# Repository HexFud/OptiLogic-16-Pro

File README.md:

# OptiLogic-16 Pro

OptiLogic-16 Pro is a custom built, FPGA-based 16-channel logic analyzer and network monitor designed from scratch from PCB design and component selection to firmware development and 3D modeling.
Featuring a Xilinx Kintex-7 FPGA 500 MSa/s sampling programmable input thresholds 4 Gbit DDR3 memory three SFP ports Gigabit Ethernet and USB 3.0, it is designed for high-speed digital signal analysis, hardware debugging, and network data acquisition.

## Schematic and PCB

### How this was made

I designed an 8-layer PCB that has 16 digital inputs united by 4 comparators. The board runs with 12V DC current with a standard barrel jack connector:

1. 16 analog thresholds programmable from -2.0V to +5.0V.
2. A 4 Gbit DDR3 memory dedicated to sample buffering.
3. Three SFP cages for fiber optic (2 are recive only and 1 is recive and trasmit).
4. Gigabit Ethernet.
5. USB 3.0 for PC communication.

The PCB has a precise layer structure:

1. **F.Cu** is only used for local connections or high speed and GND plane
2. **In1.Cu** is used as GND plane to remove noise and interferences from the under and above layer. It is used to put traces on it if there is no space between them
3. **In2.Cu** is used for short range high speed comunication like the RAM
4. **In3.Cu** is used only to carry power with very thick copper traces
5. **In4.Cu** is the same as In1.Cu
6. **In5.Cu** used to connect the comparators and DACs between them and wire them to the FGPA
7. **In6.Cu** is the same as In3.Cu
8. **B.Cu** used as auxiliary short distance traces

### External connections breakdown

1. **12V Power**: The main barrel jack socket that powers the board portectd by a resettable fuse. The 12V input is stepped down with multiple converters and the 12V input becomes +7.0V, -3.0V, +3.3V, +2.5V, +1.8V, +1.5V, +1.2V, +1.0V required by the FPGA, comparators, and transceivers.
2. **USB-C Port**: This port supports PC communication.
3. **Logic Probes**: Two 20-pin headers handling the 16 high-speed input channels. The even pins are connected to GND.
4. **JTAG**: A 14-pin socket used to debug and flash the FPGA and the QSPI memory.

### Mechanical design and why I chose certain components

To make sure the logic analyzer can sample at 500 MSa/s without struggling with signal integrity, I had to select specialized components:

* **FPGA (Xilinx Kintex-7 XC7K70T-2FBG676I)**: I choose the FBG676 package because it provides enough I/O pins to drive everything that is on the board.
* **Comparators (LMH7324)**: Selected for their 700 ps rise/fall times. By powering their output stage (`VCCO`) at +2.5V, the RSPECL outputs naturally shift to LVDS levels, allowing direct connection to the FPGA without complex external resistor networks.
* **USB Bridge (FTDI FT601Q)**: I avoided using a PCIe interface or a complex FPGA-based USB PHY. The FT601Q provides a 32-bit synchronous 245 FIFO interface running at 100 MHz, easily sustaining ~380 MB/s of real-world bandwidth to the host PC.
* **DACs (TI DAC8568)**: Chosen to provide 16 independent threshold voltages. A single SPI bus configures both chips, and precision Op-Amps scale the 0–2.5V output to the required -2.0V to +5.0V range.

### How to flash the firmware

My project doesn't have a built-in USB-to-JTAG programmer. To flash the firmware you need a Xilinx Platform Cable USB or a JTAG adapter wired to the connector. You must use the AMD/Xilinx Vivado Design Suite to upload the firmware into the QSPI Flash.

### Steps to reproduce:

**In AMD/Xilinx Vivado (Compilation):**

1. Install Vivado 2023.2 (or newer).
2. Open the project and go to the settings to select the target device `XC7K70T-2FBG676I`.
3. Add the Verilog sources and the XDC file.
4. Run Synthesis and Implementation from the left panel.
5. Click on Generate Bitstream.
6. Open the Tcl Console and paste the following command to export the compiled binary for the QSPI Flash:
`write_cfgmem -format bin -interface spix4 -size 16 -loadbit "up 0x0 ./project_name.runs/impl_1/optilogic_16_pro_top.bit" -file ./optilogic_16_pro_flash.bin`

**In Vivado Hardware Manager (Flashing):**

1. Insert the JTAG programmer into the PC and connect it to the header on the board.
2. Connect the 12V power supply.
3. In Vivado, click "Open Hardware Manager" ensure that the programmer is selected, and click "Auto Connect".
4. Right-click the `xc7k70t_0` device and select "Add Configuration Memory Device".
5. Search for the `w25q128-spi-x1_x2_x4` part and select it.
6. Go to the programming tab select the previously exported `.bin` file ensure "Erase, Program, Verify" is selected, and click "Start Programming". If everything goes right you'll see a success message. Power-cycle the board to boot the firmware.

### Filament and Thermal recommendation

The Kintex-7 FPGA, FT601Q bridge, KSZ9031 PHY, and switching regulators generate a lot of heat (50°C–60°C) during continuous sampling. The LMH7324 comparators also dissipate heat into the PCB internal GND plane. To dissipate the thermal load and shield the board from radio frequency interference the board must be enclosed in a CNC-machined aluminum case.
I suggest using these settings on JLCPCB before putting it into production

### ⚠️⚠️ Safety advice ⚠️⚠️

This project includes experimental software and hardware designs. Assembly documentation and firmware are still under development and may contain bugs, errors, or incomplete features. By using, building, or modifying this project, you acknowledge that:

1. You use this project entirely at your own risk.
2. You are solely responsible for safe assembly, testing, and operation.
3. The author isn't responsible for any type of damage, injury, or loss to people or the machine itself.

By proceeding, you accept all risks and agree to these conditions. If you do not acknowledge these risks and conditions, please do not use or build this project.

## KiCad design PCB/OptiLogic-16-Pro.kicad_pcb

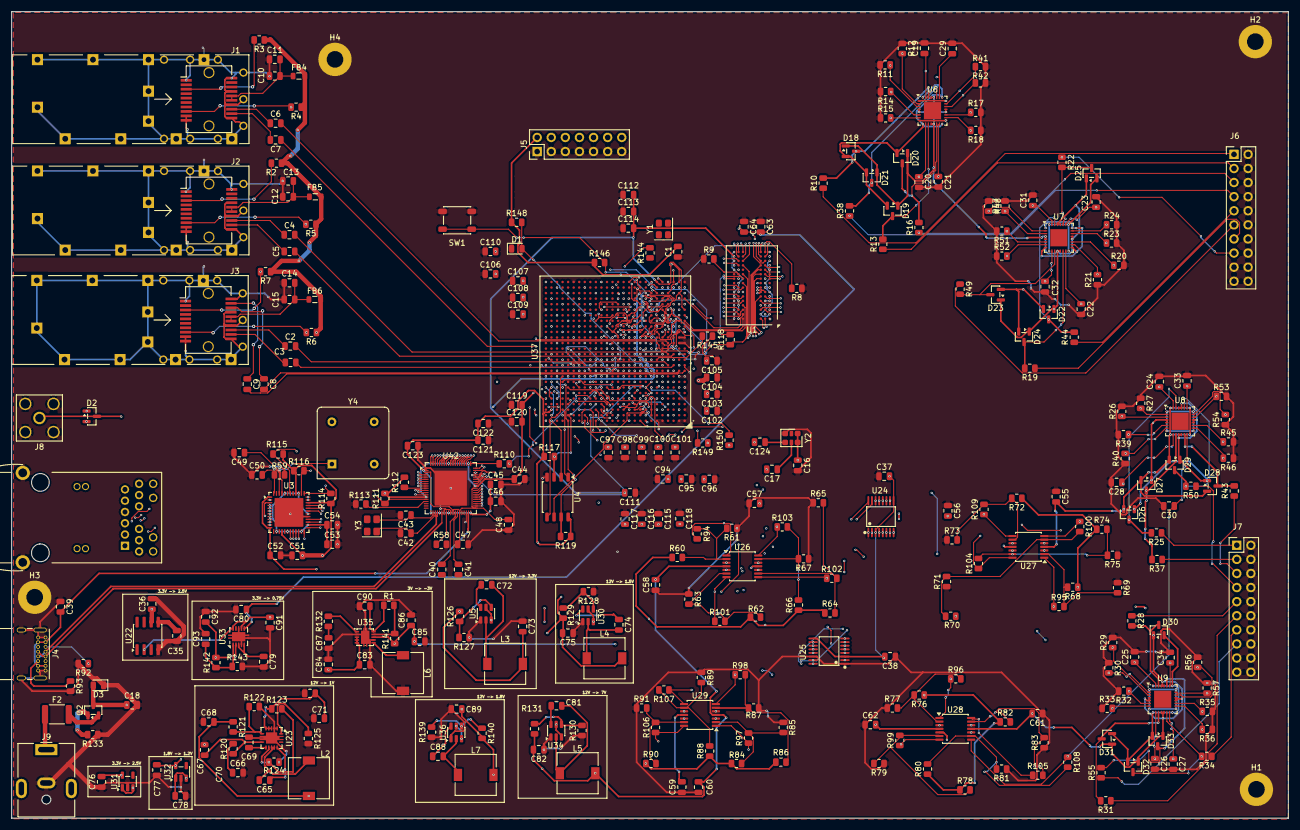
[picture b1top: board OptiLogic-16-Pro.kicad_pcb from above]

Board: 8 copper layers, 230.0 x 145.3 mm, 342 parts (0 on the bottom side), 339 nets.

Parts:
C1, C2, C3, C4, C5, C6, C7, C8, C9, C10, C12, C14, C16, C17, C19, C20, C21, C22, C23, C24, C25, C26, C27, C28, C29, C30, C31, C32, C33, C34, C37, C38, C39, C40, C41, C44, C45, C46, C48, C51, C52, C53, C55, C56, C57, C58, C59, C60, C61, C62, C63, C64, C65, C72, C74, C80, C81, C84, C88, C90, C91, C93, C94, C95, C96, C97, C98, C99, C100, C101, C102, C103, C106, C107, C108, C109, C111, C112, C113, C114, C115, C116, C117, C118, C119, C120, C121, C122, C123, C124: 100nF; C_0805_2012Metric
C11, C13, C15, C79, C83, C85, C86: 10uF; C_0805_2012Metric
C18: 100uF 25V; C_0805_2012Metric
C35, C36, C78, C92: 1uF; C_0805_2012Metric
C42, C43: 12pF; C_0805_2012Metric
C47, C54, C70, C71, C104, C105, C110: 4.7uF; C_0805_2012Metric
C49, C50: 22pF; C_0805_2012Metric
C66: 27nF; C_0805_2012Metric
C67: 43pF; C_0805_2012Metric
C68: 100uF; C_0805_2012Metric
C69: 2.2nF; C_0805_2012Metric
C73, C75, C82, C89: 22uF; C_0805_2012Metric
C76, C77: 2.2uF; C_0805_2012Metric
C87: 1nF; C_0805_2012Metric
D1: LED; LED_0805_2012Metric
D2, D18, D19, D20, D21, D22, D23, D24, D25, D26, D27, D28, D29, D30, D31, D32, D33: BAV99; SOT-23
D3: 18V; D_0805_2012Metric
F2: 3A 16V; Fuse_1812_4532Metric
FB4, FB5, FB6: FerriteBead; L_0805_2012Metric
H1, H2, H3, H4: MountingHole_Pad; MountingHole_3mm_Pad
J1, J2, J3: SFP; Connector_SFP_and_Cage
J4: USB_C_Receptacle; USB_C_Receptacle_GCT_USB4085
J5: Conn_02x07_Odd_Even; PinHeader_2x07_P2.54mm_Vertical
J6, J7: Conn_02x10_Odd_Even; PinHeader_2x10_P2.54mm_Vertical
J8: Conn_Coaxial; SMA_Amphenol_132203-12_Horizontal
J9: Barrel_Jack; BarrelJack_CUI_PJ-063AH_Horizontal
L2, L3, L5: 2.2uH; L_7.3x7.3_H3.5
L4, L7: 1.5uH; L_7.3x7.3_H3.5
L6: 4.7uH; L_7.3x7.3_H3.5
Q2: Q_PMOS_GSD; SOT-23
R1: 12.1k; R_0805_2012Metric
R2, R3, R4, R5, R6, R7, R8, R114: 4.7K; R_0805_2012Metric
R9: 240; R_0805_2012Metric
R10, R13, R16, R19, R22, R25, R28, R31, R34, R37, R38, R43, R44, R49, R50, R55, R118, R145: 100; R_0805_2012Metric
R11, R12, R14, R15, R17, R18, R20, R21, R23, R24, R26, R27, R29, R30, R32, R33, R35, R36, R39, R40, R41, R42, R45, R46, R47, R48, R51, R52, R53, R54, R56, R57: 150; R_0805_2012Metric
R58: 12k 1%; R_0805_2012Metric
R59: 12.1k 1%; R_0805_2012Metric
R60, R62, R64, R66, R68, R70, R72, R74, R76, R78, R80, R82, R84, R86, R88, R90: 15k 0.1%; R_0805_2012Metric
R61, R63, R65, R67, R69, R71, R73, R75, R77, R79, R81, R83, R85, R87, R89, R91, R94, R95, R96, R97, R98, R99, R100, R101, R102, R103, R104, R105, R106, R107, R108, R109: 12k 0.1%; R_0805_2012Metric
R92, R93: 5.1k; R_0805_2012Metric
R110: 22; R_0805_2012Metric
R111, R112, R113, R127, R128, R129, R130, R139, R142, R143: 10k; R_0805_2012Metric
R115, R116, R122: 10K; R_0805_2012Metric
R117, R119, R132, R146, R148, R149, R150: 4.7k; R_0805_2012Metric
R120: 3.57k; R_0805_2012Metric
R121: 2.49K; R_0805_2012Metric
R123: 102k; R_0805_2012Metric
R124: 36.5k; R_0805_2012Metric
R125: 107k; R_0805_2012Metric
R126: 33.2k; R_0805_2012Metric
R131: 82.5k; R_0805_2012Metric
R133: 100k; R_0805_2012Metric
R140: 13.7k; R_0805_2012Metric
R141: 30k; R_0805_2012Metric
R144: 33; R_0805_2012Metric
RJ1: RJ45-TH_0826-1X1T-HT-F
SW1: SW_Push; SW_SPST_PTS647_Sx38
U1: MT41K256M16HA; Micron_FBGA-96_9x14mm_Layout9x16_P0.8mm
U3: KSZ9031RNXCA; QFN-48-1EP_7x7mm_P0.5mm_EP5.15x5.15mm
U4: W25Q128JVS; SOIC-8_5.3x5.3mm_P1.27mm
U5, U30, U34, U36: TPS563200; SOT-23-6
U6, U7, U8, U9: LMH7324; WQFN-32-1EP_5x5mm_P0.5mm_EP3.1x3.1mm
U22: REF5025AD; SOIC-8_3.9x4.9mm_P1.27mm
U23: VQFN-14_L3.5-W3.5-P0.50-BL-EP_TPS54622RHLT
U24, U25: TSSOP-16_L5.0-W4.4-P0.65-LS6.4-BL
U26, U27, U28, U29: Opamp_Quad; TSSOP-14_4.4x5mm_P0.65mm
U31: AP2112K-2.5; SOT-23-5
U32: TLV75512PDBV; SOT-23-5
U33: TPS51200DRC; VSON-10-1EP_3x3mm_P0.5mm_EP1.65x2.4mm
U35: VSON-10_L3.0-W3.0-P0.50-TL-EP-1
U37: FBGA-676_L27.0-W27.0-R26-C26-P1.00-BL
U42: FT601Q; QFN-76-1EP_9x9mm_P0.4mm_EP5.81x6.31mm
Y1: ACO-xxxMHz; Oscillator_SMD_Abracon_ASE-4Pin_3.2x2.5mm
Y2: 125MHz; Oscillator_SMD_SiTime_PQFD-6L_3.2x2.5mm
Y3: Crystal; Crystal_SMD_3225-4Pin_3.2x2.5mm
Y4: 25.000 MHz; Oscillator_DIP-8

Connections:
+0V75_VREF: C63.2, C64.2, C80.1, U1.H1 (V_{REFDQ}), U1.M8 (V_{REFCA}), U33.6 (REFOUT)
+0V75_VTT: C79.1, U33.3 (VO), U33.5 (VOSNS)
+1V0: C68.2, C94.2, C95.2, C96.2, C97.2, C98.2, C99.2, C100.2, C101.2, C102.2, C103.2, C104.2, C105.2, L2.2, R121.1, U37.C6 (MGTAVCC), U37.E6 (MGTAVCC), U37.G6 (MGTAVCC), U37.J6 (MGTAVCC), U37.J9 (VCCINT), U37.K8 (VCCINT), U37.K10 (VCCINT), U37.K12 (VCCINT), U37.K14 (VCCINT), U37.L6 (MGTAVCC), U37.L9 (VCCINT), U37.L13 (VCCINT), U37.L15 (VCCINT), U37.M8 (VCCINT), U37.M14 (VCCINT), U37.N9 (VCCINT), U37.N13 (VCCBRAM), U37.N15 (VCCINT), U37.P14 (VCCINT), U37.R13 (VCCBRAM), U37.R15 (VCCINT), U37.T12 (VCCBRAM), U37.T14 (VCCINT), U37.U13 (VCCBRAM), U37.U15 (VCCINT)
+1V2: C53.1, C54.1, C77.2, C115.2, C116.2, C117.2, C118.2, U3.4 (AVDDL), U3.9 (AVDDL), U3.14 (DVDDL), U3.18 (DVDDL), U3.23 (DVDDL), U3.26 (DVDDL), U3.30 (DVDDL), U3.39 (DVDDL), U3.44 (AVDDL_PLL), U32.5 (OUT), U37.B3 (MGTAVTT), U37.C2 (MGTAVTT), U37.D3 (MGTAVTT), U37.G2 (MGTAVTT), U37.H3 (MGTAVTT), U37.L2 (MGTAVTT), U37.M3 (MGTAVTT), U37.M5 (MGTAVTTRCAL_115)
+1V5: C75.2, C92.2, C111.2, C112.2, C113.2, C114.2, L4.2, R129.2, R142.2, U1.A1 (V_{DDQ}), U1.A8 (V_{DDQ}), U1.B2 (V_{DD}), U1.C1 (V_{DDQ}), U1.C9 (V_{DDQ}), U1.D2 (V_{DDQ}), U1.D9 (V_{DD}), U1.E9 (V_{DDQ}), U1.F1 (V_{DDQ}), U1.G7 (V_{DD}), U1.H2 (V_{DDQ}), U1.H9 (V_{DDQ}), U1.K2 (V_{DD}), U1.K8 (V_{DD}), U1.N1 (V_{DD}), U1.N9 (V_{DD}), U1.R1 (V_{DD}), U1.R9 (V_{DD}), U33.2 (VLDOIN), U37.AA1 (VCCO_34), U37.AC5 (VCCO_34), U37.AD2 (VCCO_34), U37.AF6 (VCCO_34), U37.U3 (VCCO_34), U37.Y4 (VCCO_34)
+1V8: C78.2, C89.2, C106.2, C107.2, C108.2, C109.2, C110.2, L7.2, R140.2, U32.1 (IN), U32.3 (EN), U37.AA11 (VCCO_33), U37.AB8 (VCCO_33), U37.AB18 (VCCO_32), U37.AC15 (VCCO_32), U37.AD12 (VCCO_33), U37.AE9 (VCCO_33), U37.AE19 (VCCO_32), U37.AF16 (VCCO_32), U37.L11 (VCCAUX), U37.M10 (VCCAUX), U37.N6 (MGTVCCAUX), U37.P8 (VCCAUX_IO_G0), U37.P10 (VCCAUX), U37.R9 (VCCAUX_IO_G0), U37.T8 (VCCAUX_IO_G0), U37.T10 (VCCAUX), U37.U11 (VCCAUX), U37.V10 (VCCO_33), U37.W7 (VCCO_33), U37.W17 (VCCO_32), U37.Y14 (VCCO_32)
+2V5: C44.1, C51.2, C76.2, C119.2, C120.2, R111.2, R112.2, R114.1, R115.1, R116.1, U3.16 (DVDDH), U3.34 (DVDDH), U3.40 (DVDDH), U6.1 (VCCO), U6.8 (VCCO), U6.17 (VCCO), U6.24 (VCCO), U7.1 (VCCO), U7.8 (VCCO), U7.17 (VCCO), U7.24 (VCCO), U8.1 (VCCO), U8.8 (VCCO), U8.17 (VCCO), U8.24 (VCCO), U9.1 (VCCO), U9.8 (VCCO), U9.17 (VCCO), U9.24 (VCCO), U31.5 (VOUT), U37.A11 (VCCO_16), U37.AA21 (VCCO_12), U37.AC25 (VCCO_12), U37.AD22 (VCCO_12), U37.AF26 (VCCO_12), U37.B8 (VCCO_16), U37.B18 (VCCO_15), U37.C15 (VCCO_16), U37.D12 (VCCO_16), U37.E9 (VCCO_16), U37.E19 (VCCO_15), U37.F16 (VCCO_15), U37.G13 (VCCO_16), U37.H10 (VCCO_16), U37.H20 (VCCO_15), U37.J17 (VCCO_15), U37.K24 (VCCO_13), U37.M18 (VCCO_15), U37.N25 (VCCO_13), U37.P22 (VCCO_13), U37.R19 (VCCO_13), U37.T16 (VCCO_13), U37.T26 (VCCO_13), U37.U23 (VCCO_12), U37.V20 (VCCO_12), U37.Y24 (VCCO_12), U42.14 (VCCIO), U42.49 (VCCIO), U42.59 (VCCIO), U42.68 (VCCIO)
+3V3: C1.2, C16.1, C37.2, C38.2, C45.1, C46.1, C52.1, C73.2, C83.1, C84.1, C91.1, C121.2, C122.2, C123.2, FB4.2, FB5.2, FB6.2, J5.2, L3.2, R2.1, R3.1, R4.1, R5.1, R6.1, R7.1, R117.1, R119.1, R126.2, R146.1, R148.1, R149.1, R150.1, U3.1 (AVDDH), U3.12 (AVDDH), U4.8 (VCC), U22.2 (Vin), U24.3 (AVDD), U24.9 (CLR#), U25.3 (AVDD), U25.9 (CLR#), U31.1 (VIN), U31.3 (EN), U33.7 (EN), U33.10 (VIN), U35.3 (VIN), U35.4 (EN), U35.5 (IN), U37.A21 (VCCO_14), U37.C25 (VCCO_14), U37.D22 (VCCO_14), U37.E8 (VCCBATT_0), U37.F26 (VCCO_14), U37.G23 (VCCO_14), U37.L7 (VCCO_0), U37.L21 (VCCO_14), U37.P7 (CFGBVS_0), U37.T6 (VCCO_0), U42.2 (AVDD), U42.20 (VCC33), U42.24 (VCC33), U42.28 (VDDA), U42.38 (VCC33), Y2.1 (OE), Y2.6 (VDD)
+7V0_A: C55.2, C58.2, C60.2, C62.2, C82.2, D2.2 (A), D18.2 (A), D19.2 (A), D20.2 (A), D21.2 (A), D22.2 (A), D23.2 (A), D24.2 (A), D25.2 (A), D26.2 (A), D27.2 (A), D28.2 (A), D29.2 (A), D30.2 (A), D31.2 (A), D32.2 (A), D33.2 (A), L5.2, R131.2, U6.9 (VCCI), U6.16 (VCCI), U6.25 (VCCI), U6.32 (VCCI), U7.9 (VCCI), U7.16 (VCCI), U7.25 (VCCI), U7.32 (VCCI), U8.9 (VCCI), U8.16 (VCCI), U8.25 (VCCI), U8.32 (VCCI), U9.9 (VCCI), U9.16 (VCCI), U9.25 (VCCI), U9.32 (VCCI), U26.4 (V+), U27.4 (V+), U28.4 (V+), U29.4 (V+)
+12V_RAW: C18.1, C70.2, C71.2, D3.2 (A2), Q2.3 (D), R123.1, U5.3 (VIN), U5.5 (EN), U23.4 (PVIN), U23.5 (PVIN), U23.6 (VIN), U30.3 (VIN), U30.5 (EN), U34.3 (VIN), U34.5 (EN), U36.3 (VIN), U36.5 (EN)
-3V0_A: C56.2, C57.2, C59.2, C61.2, C85.1, C86.1, D2.1 (K), D18.1 (K), D19.1 (K), D20.1 (K), D21.1 (K), D22.1 (K), D23.1 (K), D24.1 (K), D25.1 (K), D26.1 (K), D27.1 (K), D28.1 (K), D29.1 (K), D30.1 (K), D31.1 (K), D32.1 (K), D33.1 (K), R141.1, U6.4 (VEE), U6.5 (VEE), U6.12 (VEE), U6.13 (VEE), U6.20 (VEE), U6.21 (VEE), U6.28 (VEE), U6.29 (VEE), U7.4 (VEE), U7.5 (VEE), U7.12 (VEE), U7.13 (VEE), U7.20 (VEE), U7.21 (VEE), U7.28 (VEE), U7.29 (VEE), U8.4 (VEE), U8.5 (VEE), U8.12 (VEE), U8.13 (VEE), U8.20 (VEE), U8.21 (VEE), U8.28 (VEE), U8.29 (VEE), U9.4 (VEE), U9.5 (VEE), U9.12 (VEE), U9.13 (VEE), U9.20 (VEE), U9.21 (VEE), U9.28 (VEE), U9.29 (VEE), U26.11 (V-), U27.11 (V-), U28.11 (V-), U29.11 (V-), U35.8 (OUT)
/Power_Supply/EN: R123.2, R124.1, U23.10 (EN)
/Power_Supply/FB: R1.2, R141.2, U35.9 (FB)
/Power_Supply/REFIN: C93.1, R142.1, R143.1, U33.1 (REFIN)
/Power_Supply/VREF: C90.2, R1.1, U35.10 (VREF)
/Power_Supply/VSENSE: R121.2, R122.1, U23.7 (VSENSE)
DAC_CS0_N: U24.2 (SYNC#), U37.G24 (IO_L14P_T2_SRCC_14)
DAC_CS1_N: U25.2 (SYNC#), U37.F24 (IO_L14N_T2_SRCC_14)
DAC_OUT_0: U24.4 (VOUTA), U26.3 (+)
DAC_OUT_1: U24.13 (VOUTB), U26.5 (+)
DAC_OUT_2: U24.5 (VOUTC), U26.10 (+)
DAC_OUT_3: U24.12 (VOUTD), U26.12 (+)
DAC_OUT_4: U24.6 (VOUTE), U27.3 (+)
DAC_OUT_5: U24.11 (VOUTF), U27.5 (+)
DAC_OUT_6: U24.7 (VOUTG), U27.10 (+)
DAC_OUT_7: U24.10 (VOUTH), U27.12 (+)
DAC_OUT_8: U25.4 (VOUTA), U28.3 (+)
DAC_OUT_9: U25.13 (VOUTB), U28.5 (+)
DAC_OUT_10: U25.5 (VOUTC), U28.10 (+)
DAC_OUT_11: U25.12 (VOUTD), U28.12 (+)
DAC_OUT_12: U25.6 (VOUTE), U29.3 (+)
DAC_OUT_13: U25.11 (VOUTF), U29.5 (+)
DAC_OUT_14: U25.7 (VOUTG), U29.10 (+)
DAC_OUT_15: U25.10 (VOUTH), U29.12 (+)
DAC_SPI_MOSI: U24.15 (DIN), U25.15 (DIN), U37.F23 (IO_L13N_T2_MRCC_14)
DAC_SPI_SCLK: U24.16 (SCLK), U25.16 (SCLK), U37.G22 (IO_L13P_T2_MRCC_14)
DDR_A0: U1.N3 (A0), U37.AF2 (IO_L24N_T3_34)
DDR_A1: U1.P7 (A1), U37.AF3 (IO_L24P_T3_34)
DDR_A2: U1.P3 (A2), U37.AE5 (IO_L23N_T3_34)
DDR_A3: U1.N2 (A3), U37.AE6 (IO_L23P_T3_34)
DDR_A4: U1.P8 (A4), U37.AE2 (IO_L22N_T3_34)
DDR_A5: U1.P2 (A5), U37.AE3 (IO_L22P_T3_34)
DDR_A6: U1.R8 (A6), U37.AF4 (IO_L21N_T3_DQS_34)
DDR_A7: U1.R2 (A7), U37.AF5 (IO_L21P_T3_DQS_34)
DDR_A8: U1.T8 (A8), U37.AE1 (IO_L20N_T3_34)
DDR_A9: U1.R3 (A9), U37.AD1 (IO_L20P_T3_34)
DDR_A10: U1.L7 (A10/AP), U37.AD3 (IO_L19N_T3_VREF_34)
DDR_A11: U1.R7 (A11), U37.AD5 (IO_L18N_T2_34)
DDR_A12: U1.N7 (A12/~BC), U37.AD6 (IO_L18P_T2_34)
DDR_A13: U1.T3 (A13), U37.Y5 (IO_L17N_T2_34)
DDR_A14: U1.T7 (A14), U37.Y6 (IO_L17P_T2_34)
DDR_BA0: U1.M2 (BA0), U37.AC6 (IO_L16N_T2_34)
DDR_BA1: U1.N8 (BA1), U37.AB6 (IO_L16P_T2_34)
DDR_BA2: U1.M3 (BA2), U37.AB5 (IO_L15N_T2_DQS_34)
DDR_CAS_N: U1.K3 (~CAS), U37.AC3 (IO_L14N_T2_SRCC_34)
DDR_CKE: U1.K9 (CKE), U37.AA4 (IO_L13P_T2_MRCC_34)
DDR_CK_N: R118.2, U1.K7 (~CK), U37.AA2 (IO_L12N_T1_MRCC_34)
DDR_CK_P: R118.1, U1.J7 (CK), U37.AA3 (IO_L12P_T1_MRCC_34)
DDR_CS_N: U1.L2 (~CS), U37.AB4 (IO_L13N_T2_MRCC_34)
DDR_DQ0: U1.E3 (DQ0), U37.U6 (IO_L1P_T0_34)
DDR_DQ1: U1.F7 (DQ1), U37.U5 (IO_L1N_T0_34)
DDR_DQ2: U1.F2 (DQ2), U37.U2 (IO_L2P_T0_34)
DDR_DQ3: U1.F8 (DQ3), U37.U1 (IO_L2N_T0_34)
DDR_DQ4: U1.H3 (DQ4), U37.V3 (IO_L4P_T0_34)
DDR_DQ5: U1.H8 (DQ5), U37.W3 (IO_L4N_T0_34)
DDR_DQ6: U1.G2 (DQ6), U37.U7 (IO_L5P_T0_34)
DDR_DQ7: U1.H7 (DQ7), U37.V6 (IO_L5N_T0_34)
DDR_DQ8: U1.D7 (DQ8), U37.Y3 (IO_L7P_T1_34)
DDR_DQ9: U1.C3 (DQ9), U37.Y2 (IO_L7N_T1_34)
DDR_DQ10: U1.C8 (DQ10), U37.V2 (IO_L8P_T1_34)
DDR_DQ11: U1.C2 (DQ11), U37.V1 (IO_L8N_T1_34)
DDR_DQ12: U1.A7 (DQ12), U37.W1 (IO_L10P_T1_34)
DDR_DQ13: U1.A2 (DQ13), U37.Y1 (IO_L10N_T1_34)
DDR_DQ14: U1.B8 (DQ14), U37.AB2 (IO_L11P_T1_SRCC_34)
DDR_DQ15: U1.A3 (DQ15), U37.AC2 (IO_L11N_T1_SRCC_34)
DDR_LDM: U1.E7 (LDM), U37.V4 (IO_L6P_T0_34)
DDR_LDQS_N: U1.G3 (~LDQS), U37.W5 (IO_L3N_T0_DQS_34)
DDR_LDQS_P: U1.F3 (LDQS), U37.W6 (IO_L3P_T0_DQS_34)
DDR_ODT: U1.K1 (ODT), U37.T7 (IO_25_VRP_34)
DDR_RAS_N: U1.J3 (~RAS), U37.AA5 (IO_L15P_T2_DQS_34)
DDR_RESET_N: R8.2, U1.T2 (~RESET), U37.AD4 (IO_L19P_T3_34)
DDR_UDM: U1.D3 (UDM), U37.W4 (IO_L6N_T0_VREF_34)
DDR_UDQS_N: U1.B7 (~UDQS), U37.AC1 (IO_L9N_T1_DQS_34)
DDR_UDQS_P: U1.C7 (UDQS), U37.AB1 (IO_L9P_T1_DQS_34)
DDR_WE_N: U1.L3 (~WE), U37.AC4 (IO_L14P_T2_SRCC_34)
FPGA_CCLK: U4.6 (CLK), U37.C8 (CCLK_0)
FPGA_D00_MOSI: U4.5 (DI/IO_{0}), U37.B24 (IO_L1P_T0_D00_MOSI_14), U37.J23 (IO_L24N_T3_A00_D16_14)
FPGA_D01_DIN: U4.2 (DO/IO_{1}), U37.A25 (IO_L1N_T0_D01_DIN_14), U37.J24 (IO_L22P_T3_A05_D21_14)
FPGA_D02: R117.2, U4.3 (~WP/IO_{2}), U37.B22 (IO_L2P_T0_D02_14), U37.H23 (IO_L20P_T3_A08_D24_14)
FPGA_D03: R119.2, U4.7 (~HOLD/~RESET/IO_{3}), U37.A22 (IO_L2N_T0_D03_14), U37.H24 (IO_L20N_T3_A07_D23_14)
FPGA_FCS_B: U4.1 (~CS), U37.C23 (IO_L6P_T0_FCS_B_14), U37.L23 (IO_25_14)
FT_BE0: U37.G17 (IO_L11P_T1_SRCC_AD12P_15), U42.4 (BE_0)
FT_BE1: U37.F17 (IO_L12P_T1_MRCC_AD5P_15), U42.5 (BE_1)
FT_BE2: U37.E17 (IO_L12N_T1_MRCC_AD5N_15), U42.6 (BE_2)
FT_BE3: U37.K15 (IO_0_15), U42.7 (BE_3)
FT_CLK: R110.2, U37.E18 (IO_L13P_T2_MRCC_15)
FT_DATA0: U37.C16 (IO_L1P_T0_AD0P_15), U42.40 (DATA_0)
FT_DATA1: U37.B16 (IO_L1N_T0_AD0N_15), U42.41 (DATA_1)
FT_DATA2: U37.A18 (IO_L2P_T0_AD8P_15), U42.42 (DATA_2)
FT_DATA3: U37.A19 (IO_L2N_T0_AD8N_15), U42.43 (DATA_3)
FT_DATA4: U37.B17 (IO_L3P_T0_DQS_AD1P_15), U42.44 (DATA_4)
FT_DATA5: U37.A17 (IO_L3N_T0_DQS_AD1N_15), U42.45 (DATA_5)
FT_DATA6: U37.C17 (IO_L5P_T0_AD2P_15), U42.46 (DATA_6)
FT_DATA7: U37.C18 (IO_L5N_T0_AD2N_15), U42.47 (DATA_7)
FT_DATA8: U37.D15 (IO_L6P_T0_15), U42.50 (DATA_8)
FT_DATA9: U37.D16 (IO_L6N_T0_VREF_15), U42.51 (DATA_9)
FT_DATA10: U37.H16 (IO_L7P_T1_AD10P_15), U42.52 (DATA_10)
FT_DATA11: U37.G16 (IO_L7N_T1_AD10N_15), U42.53 (DATA_11)
FT_DATA12: U37.G15 (IO_L8P_T1_AD3P_15), U42.54 (DATA_12)
FT_DATA13: U37.F15 (IO_L8N_T1_AD3N_15), U42.55 (DATA_13)
FT_DATA14: U37.J15 (IO_L9P_T1_DQS_AD11P_15), U42.56 (DATA_14)
FT_DATA15: U37.J16 (IO_L9N_T1_DQS_AD11N_15), U42.57 (DATA_15)
FT_DATA16: U37.E15 (IO_L10P_T1_AD4P_15), U42.60 (DATA_16)
FT_DATA17: U37.E16 (IO_L10N_T1_AD4N_15), U42.61 (DATA_17)
FT_DATA18: U37.M16 (IO_25_15), U42.62 (DATA_18)
FT_DATA19: U37.K18 (IO_L24N_T3_RS0_15), U42.63 (DATA_19)
FT_DATA20: U37.L17 (IO_L24P_T3_RS1_15), U42.64 (DATA_20)
FT_DATA21: U37.L18 (IO_L23N_T3_FWE_B_15), U42.65 (DATA_21)
FT_DATA22: U37.M17 (IO_L23P_T3_FOE_B_15), U42.66 (DATA_22)
FT_DATA23: U37.K17 (IO_L22N_T3_A16_15), U42.67 (DATA_23)
FT_DATA24: U37.K16 (IO_L22P_T3_A17_15), U42.69 (DATA_24)
FT_DATA25: U37.L20 (IO_L21N_T3_DQS_A18_15), U42.70 (DATA_25)
FT_DATA26: U37.L19 (IO_L21P_T3_DQS_15), U42.71 (DATA_26)
FT_DATA27: U37.J19 (IO_L20N_T3_A19_15), U42.72 (DATA_27)
FT_DATA28: U37.J18 (IO_L20P_T3_A20_15), U42.73 (DATA_28)
FT_DATA29: U37.J20 (IO_L19N_T3_A21_VREF_15), U42.74 (DATA_29)
FT_DATA30: U37.K20 (IO_L19P_T3_A22_15), U42.75 (DATA_30)
FT_DATA31: U37.G20 (IO_L18N_T2_A23_15), U42.76 (DATA_31)
FT_OE_N: U37.F18 (IO_L11N_T1_SRCC_AD12N_15), U42.13 (~OE)
FT_RD_N: U37.D18 (IO_L13N_T2_MRCC_15), U42.12 (~RD)
FT_RESET_N: R111.1, U37.H18 (IO_L14N_T2_SRCC_15), U42.15 (~RESET)
FT_RXF_N: U37.B19 (IO_L4N_T0_AD9N_15), U42.9 (~RXF)
FT_TXE_N: U37.C19 (IO_L4P_T0_AD9P_15), U42.8 (~TXE)
FT_WR_N: U37.H17 (IO_L14P_T2_SRCC_15), U42.11 (~WR)
GND: C1.1, C10.1, C11.1, C12.1, C13.1, C14.1, C15.1, C16.2, C18.2, C19.2, C20.2, C21.2, C22.2, C23.2, C24.2, C25.2, C26.2, C27.2, C28.2, C29.2, C30.2, C31.2, C32.2, C33.2, C34.2, C35.2, C36.2, C37.1, C38.1, C39.1, C42.1, C43.2, C44.2, C45.2, C46.2, C47.2, C48.1, C49.2, C50.1, C51.1, C52.2, C53.2, C54.2, C55.1, C56.1, C57.1, C58.1, C59.1, C60.1, C61.1, C62.1, C63.1, C64.1, C66.2, C67.2, C68.1, C69.2, C70.1, C71.1, C73.1, C75.1, C76.1, C77.1, C78.1, C79.2, C80.2, C82.1, C83.2, C84.2, C85.2, C86.2, C87.1, C89.1, C90.1, C91.2, C92.1, C93.2, C94.1, C95.1, C96.1, C97.1, C98.1, C99.1, C100.1, C101.1, C102.1, C103.1, C104.1, C105.1, C106.1, C107.1, C108.1, C109.1, C110.1, C111.1, C112.1, C113.1, C114.1, C115.1, C116.1, C117.1, C118.1, C119.1, C120.1, C121.1, C122.1, C123.1, D1.1 (K), D3.1 (A1), H1.1 (1_1), H2.1 (1_1), H3.1 (1_1), H4.1 (1_1), J1.1 (VeeT), J1.9 (VeeR), J1.10 (VeeR), J1.11 (VeeR), J1.14 (VeeR), J1.17 (VeeT), J1.20 (VeeT), J1.CAGE, J2.1 (VeeT), J2.9 (VeeR), J2.10 (VeeR), J2.11 (VeeR), J2.14 (VeeR), J2.17 (VeeT), J2.20 (VeeT), J2.CAGE, J3.1 (VeeT), J3.9 (VeeR), J3.10 (VeeR), J3.11 (VeeR), J3.14 (VeeR), J3.17 (VeeT), J3.20 (VeeT), J3.CAGE, J4.A1 (GND), J4.A12 (GND), J4.B1 (GND), J4.B12 (GND), J4.SH (SHIELD), J5.1, J5.3, J5.5, J5.7, J5.9, J5.11, J5.13, J6.2, J6.4, J6.6, J6.8, J6.10, J6.12, J6.14, J6.16, J6.17, J6.18, J6.19, J6.20, J7.2, J7.4, J7.6, J7.8, J7.10, J7.12, J7.14, J7.16, J7.17, J7.18, J7.19, J7.20, J8.2 (Ext), J9.2, L6.2, R8.1, R9.1, R11.2, R12.1, R14.2, R15.1, R17.2, R18.1, R20.2, R21.1, R23.2, R24.1, R26.2, R27.1, R29.2, R30.1, R32.2, R33.1, R35.2, R36.1, R39.2, R40.1, R41.2, R42.1, R45.2, R46.1, R47.2, R48.1, R51.2, R52.1, R53.2, R54.1, R56.2, R57.1, R58.2, R59.2, R61.1, R63.1, R65.1, R67.1, R69.1, R71.1, R73.1, R75.1, R77.1, R79.1, R81.1, R83.1, R85.1, R87.1, R89.1, R91.1, R92.2, R93.2, R113.2, R122.2, R124.2, R125.2, R127.1, R128.1, R130.1, R133.1, R139.1, R143.2, R145.1, RJ1.S1, RJ1.S2, SW1.2, U1.A9 (V_{SS}), U1.B1 (V_{SSQ}), U1.B3 (V_{SS}), U1.B9 (V_{SSQ}), U1.D1 (V_{SSQ}), U1.D8 (V_{SSQ}), U1.E1 (V_{SS}), U1.E2 (V_{SSQ}), U1.E8 (V_{SSQ}), U1.F9 (V_{SSQ}), U1.G1 (V_{SSQ}), U1.G8 (V_{SS}), U1.G9 (V_{SSQ}), U1.J2 (V_{SS}), U1.J8 (V_{SS}), U1.M1 (V_{SS}), U1.M9 (V_{SS}), U1.P1 (V_{SS}), U1.P9 (V_{SS}), U1.T1 (V_{SS}), U1.T9 (V_{SS}), U3.29 (VSS), U3.49 (PAD_GND), U4.4 (GND), U5.1 (GND), U22.4 (GND), U23.2 (GND), U23.3 (GND), U23.15 (EP), U24.1 (LDAC#), U24.14 (GND), U25.1 (LDAC#), U25.14 (GND), U30.1 (GND), U31.2 (GND), U32.2 (GND), U33.4 (GND), U33.8 (GND), U33.11 (GND), U34.1 (GND), U35.2 (GND), U35.7 (PS_GND), U35.11 (GND), U36.1 (GND), U37.A1 (GND), U37.A2 (GND), U37.A5 (GND), U37.A6 (GND), U37.A7 (GND), U37.A16 (GND), U37.A26 (GND), U37.AA6 (GND), U37.AA16 (GND), U37.AA26 (GND), U37.AB3 (GND), U37.AB13 (GND), U37.AB23 (GND), U37.AC10 (GND), U37.AC20 (GND), U37.AD7 (GND), U37.AD17 (GND), U37.AE4 (GND), U37.AE14 (GND), U37.AE24 (GND), U37.AF1 (GND), U37.AF11 (GND), U37.AF21 (GND), U37.B4 (GND), U37.B7 (GND), U37.B13 (GND), U37.B23 (GND), U37.C1 (GND), U37.C5 (GND), U37.C7 (GND), U37.C10 (GND), U37.C20 (GND), U37.D4 (GND), U37.D7 (GND), U37.D17 (GND), U37.E1 (GND), U37.E2 (GND), U37.E5 (GND), U37.E7 (GND), U37.E14 (GND), U37.E24 (GND), U37.F3 (GND), U37.F4 (GND), U37.F7 (GND), U37.F11 (GND), U37.F21 (GND), U37.G1 (GND), U37.G5 (GND), U37.G8 (GND), U37.G18 (GND), U37.H4 (GND), U37.H7 (GND), U37.H15 (GND), U37.H25 (GND), U37.J1 (GND), U37.J2 (GND), U37.J5 (GND), U37.J12 (GND), U37.J22 (GND), U37.K3 (GND), U37.K4 (GND), U37.K7 (GND), U37.K9 (GND), U37.K11 (GND), U37.K13 (GND), U37.K19 (GND), U37.L1 (GND), U37.L5 (GND), U37.L10 (GND), U37.L12 (GND), U37.L14 (GND), U37.L16 (GND), U37.L26 (GND), U37.M4 (GND), U37.M7 (GND), U37.M9 (GND), U37.M13 (GND), U37.M15 (GND), U37.M23 (GND), U37.N1 (GND), U37.N2 (GND), U37.N5 (GND), U37.N7 (GND), U37.N10 (GND), U37.N14 (GND), U37.N20 (GND), U37.P3 (GND), U37.P4 (GND), U37.P5 (M2_0), U37.P9 (GND), U37.P13 (GND), U37.P15 (GND), U37.P17 (GND), U37.R1 (GND), U37.R2 (GND), U37.R5 (GND), U37.R8 (GND), U37.R10 (GND), U37.R14 (GND), U37.R24 (GND), U37.T1 (GND), U37.T2 (M1_0), U37.T3 (GND), U37.T4 (GND), U37.T9 (GND), U37.T11 (GND), U37.T13 (GND), U37.T15 (GND), U37.T21 (GND), U37.U8 (GND), U37.U10 (GND), U37.U12 (GND), U37.U14 (GND), U37.U18 (GND), U37.V5 (GND), U37.V15 (GND), U37.V25 (GND), U37.W2 (GND), U37.W12 (GND), U37.W22 (GND), U37.Y9 (GND), U37.Y19 (GND), U42.1 (GND), U42.26 (GND), U42.29 (GND), U42.36 (GND), U42.77 (GND), Y2.3 (GND)
INGRESSO_SONDA_0: J6.1, R10.1
INGRESSO_SONDA_1: J6.3, R13.1
INGRESSO_SONDA_2: J6.5, R16.1
INGRESSO_SONDA_3: J6.7, R38.1
INGRESSO_SONDA_4: J6.9, R44.1
INGRESSO_SONDA_5: J6.11, R49.1
INGRESSO_SONDA_6: J6.13, R19.1
INGRESSO_SONDA_7: J6.15, R22.1
INGRESSO_SONDA_8: J7.1, R25.1
INGRESSO_SONDA_9: J7.3, R37.1
INGRESSO_SONDA_10: J7.5, R43.1
INGRESSO_SONDA_11: J7.7, R50.1
INGRESSO_SONDA_12: J7.9, R28.1
INGRESSO_SONDA_13: J7.11, R31.1
INGRESSO_SONDA_14: J7.13, R34.1
INGRESSO_SONDA_15: J7.15, R55.1
JTAG_TCK: J5.6, U37.L8 (TCK_0)
JTAG_TDI: J5.10, U37.R6 (TDI_0)
JTAG_TDO: J5.8, U37.R7 (TDO_0)
JTAG_TMS: J5.4, U37.N8 (TMS_0)
MDC: U3.36 (MDC), U37.F14 (IO_L15P_T2_DQS_16)
MDIO: R114.2, U3.37 (MDIO), U37.F13 (IO_L15N_T2_DQS_16)
MGT_REFCLK_N: C17.2, U37.H5 (MGTREFCLK0N_115)
MGT_REFCLK_P: C124.2, U37.H6 (MGTREFCLK0P_115)
MGT_RX0_N: C7.1, U37.R3 (MGTXRXN0_115)
MGT_RX0_P: C6.2, U37.R4 (MGTXRXP0_115)
MGT_RX1_N: C5.2, U37.N3 (MGTXRXN1_115)
MGT_RX1_P: C4.2, U37.N4 (MGTXRXP1_115)
MGT_RX2_N: C3.2, U37.L3 (MGTXRXN2_115)
MGT_RX2_P: C2.2, U37.L4 (MGTXRXP2_115)
MGT_TX2_N: C9.2, U37.K1 (MGTXTXN2_115)
MGT_TX2_P: C8.2, U37.K2 (MGTXTXP2_115)
unnamed: C65.2, L2.1, U23.11 (PH), U23.12 (PH)
unnamed: C66.1, R120.2
unnamed: C87.2, R132.1
unnamed: D1.2 (A), R148.2, U37.J7 (DONE_0)
unnamed: F2.1, J9.1
unnamed: C6.1, J1.13 (RD+)
unnamed: C7.2, J1.12 (RD-)
unnamed: J1.3 (TX_DISABLE), R3.2
unnamed: C10.2, C11.2, FB4.1, J1.15 (VccR), J1.16 (VccT)
unnamed: C4.1, J2.13 (RD+)
unnamed: C5.1, J2.12 (RD-)
unnamed: J2.3 (TX_DISABLE), R2.2
unnamed: C12.2, C13.2, FB5.1, J2.15 (VccR), J2.16 (VccT)
unnamed: C2.1, J3.13 (RD+)
unnamed: C3.1, J3.12 (RD-)
unnamed: C8.1, J3.18 (TD+)
unnamed: C9.1, J3.19 (TD-)
unnamed: C14.2, C15.2, FB6.1, J3.15 (VccR), J3.16 (VccT)
unnamed: J4.A5 (CC1), R92.1
unnamed: J4.B5 (CC2), R93.1
unnamed: Q2.1 (G), R133.2
unnamed: F2.2, Q2.2 (S)
unnamed: R9.2, U1.L8 (ZQ)
unnamed: R59.1, U3.48 (ISET)
unnamed: C50.2, U3.46 (XI), Y4.1 (1_1)
unnamed: C49.1, U3.45 (XO)
unnamed: C72.2, L3.1, U5.2 (SW)
unnamed: C72.1, U5.6 (VBST)
unnamed: R126.1, R127.2, U5.4 (VFB)
unnamed: D18.3 (K), R10.2, U6.30 (+)
unnamed: D19.3 (K), R13.2, U6.11 (+)
unnamed: D20.3 (K), R16.2, U6.14 (+)
unnamed: D21.3 (K), R38.2, U6.27 (+)
unnamed: D22.3 (K), R44.2, U7.30 (+)
unnamed: D23.3 (K), R49.2, U7.11 (+)
unnamed: D24.3 (K), R19.2, U7.14 (+)
unnamed: D25.3 (K), R22.2, U7.27 (+)
unnamed: D26.3 (K), R25.2, U8.30 (+)
unnamed: D27.3 (K), R37.2, U8.11 (+)
unnamed: D28.3 (K), R43.2, U8.14 (+)
unnamed: D29.3 (K), R50.2, U8.27 (+)
unnamed: D30.3 (K), R28.2, U9.30 (+)
unnamed: D31.3 (K), R31.2, U9.11 (+)
unnamed: D32.3 (K), R34.2, U9.14 (+)
unnamed: D33.3 (K), R55.2, U9.27 (+)
unnamed: C35.1, U22.5 (Trim/NR)
unnamed: C65.1, U23.13 (BOOT)
unnamed: C67.1, R120.1, U23.8 (COMP)
unnamed: R125.1, U23.1 (RT/CLK)
unnamed: C69.1, U23.9 (SS/TR)
unnamed: R60.2, R61.2, R94.2, U26.2 (-)
unnamed: R62.2, R63.2, R101.2, U26.6 (-)
unnamed: R64.2, R65.2, R102.2, U26.9 (-)
unnamed: R66.2, R67.2, R103.2, U26.13 (-)
unnamed: R68.2, R69.2, R95.2, U27.2 (-)
unnamed: R70.2, R71.2, R100.2, U27.6 (-)
unnamed: R72.2, R73.2, R109.2, U27.9 (-)
unnamed: R74.2, R75.2, R104.2, U27.13 (-)
unnamed: R76.2, R77.2, R96.2, U28.2 (-)
unnamed: R78.2, R79.2, R99.2, U28.6 (-)
unnamed: R80.2, R81.2, R108.2, U28.9 (-)
unnamed: R82.2, R83.2, R105.2, U28.13 (-)
unnamed: R84.2, R85.2, R97.2, U29.2 (-)
unnamed: R86.2, R87.2, R98.2, U29.6 (-)
unnamed: R88.2, R89.2, R107.2, U29.9 (-)
unnamed: R90.2, R91.2, R106.2, U29.13 (-)
unnamed: C74.2, L4.1, U30.2 (SW)
unnamed: C74.1, U30.6 (VBST)
unnamed: R128.2, R129.1, U30.4 (VFB)
unnamed: C81.2, L5.1, U34.2 (SW)
unnamed: C81.1, U34.6 (VBST)
unnamed: R130.2, R131.1, U34.4 (VFB)
unnamed: R132.2, U35.1 (COMP)
unnamed: L6.1, U35.6 (SW)
unnamed: C88.2, L7.1, U36.2 (SW)
unnamed: C88.1, U36.6 (VBST)
unnamed: R139.2, R140.1, U36.4 (VFB)
unnamed: R150.2, U37.G7 (INIT_B_0)
unnamed: R149.2, U37.T5 (M0_0)
unnamed: R146.2, SW1.1, U37.P6 (PROGRAM_B_0)
unnamed: R145.2, U37.M6 (MGTRREF_115)
unnamed: R110.1, U42.58 (CLK)
unnamed: C47.1, C48.2, U42.3 (VD10), U42.30 (VD10), U42.33 (VD10), U42.39 (DV10), U42.48 (VD10)
unnamed: R58.1, U42.27 (RREF)
unnamed: C40.2, U42.31 (TODN)
unnamed: C41.2, U42.32 (TODP)
unnamed: C39.2, J4.A4 (VBUS), J4.A9 (VBUS), J4.B4 (VBUS), J4.B9 (VBUS), U42.37 (VBUS)
unnamed: C43.1, U42.21 (XI), Y3.2
unnamed: C42.2, U42.22 (XO), Y3.1
unnamed: R112.1, U42.10 (~SIWU)
unnamed: R113.1, U42.16 (~WAKEUP)
unnamed: C124.1, Y2.4 (OUT+)
unnamed: C17.1, Y2.5 (OUT-)
PHY_INT_N: R116.2, U3.38 (INT_N/PME_N2), U37.E11 (IO_L14P_T2_SRCC_16)
PHY_RESET_N: R115.2, U3.42 (RESET_N), U37.D11 (IO_L14N_T2_SRCC_16)
RGMII_RXC: U3.35 (RX_CLK/PHYAD2), U37.E10 (IO_L12P_T1_MRCC_16)
RGMII_RXD0: U3.32 (RXD0/MODE0), U37.G11 (IO_L11P_T1_SRCC_16)
RGMII_RXD1: U3.31 (RXD1/MODE1), U37.F10 (IO_L11N_T1_SRCC_16)
RGMII_RXD2: U3.28 (RXD2/MODE2), U37.C9 (IO_L10P_T1_16)
RGMII_RXD3: U3.27 (RXD3/MODE3), U37.B9 (IO_L10N_T1_16)
RGMII_RX_CTL: U3.33 (RX_DV/CLK125_EN), U37.D10 (IO_L12N_T1_MRCC_16)
RGMII_TXC: U3.24 (GTX_CLK), U37.A9 (IO_L9P_T1_DQS_16)
RGMII_TXD0: U3.19 (TXD0), U37.D9 (IO_L8P_T1_16)
RGMII_TXD1: U3.20 (TXD1), U37.D8 (IO_L8N_T1_16)
RGMII_TXD2: U3.21 (TXD2), U37.C11 (IO_L13N_T2_MRCC_16)
RGMII_TXD3: U3.22 (TXD3), U37.C12 (IO_L13P_T2_MRCC_16)
RGMII_TX_CTL: U3.25 (TX_EN), U37.A8 (IO_L9N_T1_DQS_16)
SFP1_LOS: J1.8 (RX_LOS), R4.2, U37.E25 (IO_L15P_T2_DQS_RDWR_B_14), U37.G25 (IO_L16P_T2_CSI_B_14)
SFP2_LOS: J2.8 (RX_LOS), R5.2, U37.B25 (IO_L3P_T0_DQS_PUDC_B_14), U37.G26 (IO_L16N_T2_A15_D31_14)
SFP3_LOS: J3.8 (RX_LOS), R6.2, U37.J26 (IO_L18P_T2_A12_D28_14)
SFP3_TXDIS: J3.3 (TX_DISABLE), R7.2, U37.E26 (IO_L17N_T2_A13_D29_14)
SOGLIA_VTH_0: C19.1, R94.1, U6.31 (-), U26.1
SOGLIA_VTH_1: C20.1, R101.1, U6.10 (-), U26.7
SOGLIA_VTH_2: C21.1, R102.1, U6.15 (-), U26.8
SOGLIA_VTH_3: C29.1, R103.1, U6.26 (-), U26.14
SOGLIA_VTH_4: C31.1, R95.1, U7.31 (-), U27.1
SOGLIA_VTH_5: C32.1, R100.1, U7.10 (-), U27.7
SOGLIA_VTH_6: C22.1, R109.1, U7.15 (-), U27.8
SOGLIA_VTH_7: C23.1, R104.1, U7.26 (-), U27.14
SOGLIA_VTH_8: C24.1, R96.1, U8.31 (-), U28.1
SOGLIA_VTH_9: C28.1, R99.1, U8.10 (-), U28.7
SOGLIA_VTH_10: C30.1, R108.1, U8.15 (-), U28.8
SOGLIA_VTH_11: C33.1, R105.1, U8.26 (-), U28.14
SOGLIA_VTH_12: C25.1, R97.1, U9.31 (-), U29.1
SOGLIA_VTH_13: C26.1, R98.1, U9.10 (-), U29.7
SOGLIA_VTH_14: C27.1, R107.1, U9.15 (-), U29.8
SOGLIA_VTH_15: C34.1, R106.1, U9.26 (-), U29.14
SYSCLK_100M: R144.2, U37.AC9 (IO_L12P_T1_MRCC_33)
TRIG_IN: D2.3 (K), J8.1 (In), U37.AD9 (IO_L12N_T1_MRCC_33)
TXRXM_A: RJ1.2, U3.3 (TXRXM_A)
TXRXM_B: RJ1.4, U3.6 (TXRXM_B)
TXRXM_C: RJ1.6, U3.8 (TXRXM_C)
TXRXM_D: RJ1.8, U3.11 (TXRXM_D)
TXRXP_A: RJ1.1, U3.2 (TXRXP_A)
TXRXP_B: RJ1.3, U3.5 (TXRXP_B)
TXRXP_C: RJ1.5, U3.7 (TXRXP_C)
TXRXP_D: RJ1.7, U3.10 (TXRXP_D)
USB_DM: J4.A7 (D-), J4.B7 (D-), U42.25 (DM)
USB_DP: J4.A6 (D+), J4.B6 (D+), U42.23 (DP)
USCITA_FPGA_0_N: R12.2, U6.2 (~Q), U37.W11 (IO_L1N_T0_33)
USCITA_FPGA_0_P: R11.1, U6.3 (Q), U37.V11 (IO_L1P_T0_33)
USCITA_FPGA_1_N: R15.2, U6.7 (~Q), U37.V7 (IO_L2N_T0_33)
USCITA_FPGA_1_P: R14.1, U6.6 (Q), U37.V8 (IO_L2P_T0_33)
USCITA_FPGA_2_N: R18.2, U6.18 (~Q), U37.W9 (IO_L3N_T0_DQS_33)
USCITA_FPGA_2_P: R17.1, U6.19 (Q), U37.W10 (IO_L3P_T0_DQS_33)
USCITA_FPGA_3_N: R42.2, U6.23 (~Q), U37.Y7 (IO_L4N_T0_33)
USCITA_FPGA_3_P: R41.1, U6.22 (Q), U37.Y8 (IO_L4P_T0_33)
USCITA_FPGA_4_N: R48.2, U7.2 (~Q), U37.Y10 (IO_L5N_T0_33)
USCITA_FPGA_4_P: R47.1, U7.3 (Q), U37.Y11 (IO_L5P_T0_33)
USCITA_FPGA_5_N: R52.2, U7.7 (~Q), U37.W8 (IO_L6N_T0_VREF_33)
USCITA_FPGA_5_P: R51.1, U7.6 (Q), U37.V9 (IO_L6P_T0_33)
USCITA_FPGA_6_N: R21.2, U7.18 (~Q), U37.AF7 (IO_L7N_T1_33)
USCITA_FPGA_6_P: R20.1, U7.19 (Q), U37.AE7 (IO_L7P_T1_33)
USCITA_FPGA_7_N: R24.2, U7.23 (~Q), U37.AA7 (IO_L8N_T1_33)
USCITA_FPGA_7_P: R23.1, U7.22 (Q), U37.AA8 (IO_L8P_T1_33)
USCITA_FPGA_8_N: R27.2, U8.2 (~Q), U37.AD8 (IO_L9N_T1_DQS_33)
USCITA_FPGA_8_P: R26.1, U8.3 (Q), U37.AC8 (IO_L9P_T1_DQS_33)
USCITA_FPGA_9_N: R40.2, U8.7 (~Q), U37.AC7 (IO_L10N_T1_33)
USCITA_FPGA_9_P: R39.1, U8.6 (Q), U37.AB7 (IO_L10P_T1_33)
USCITA_FPGA_10_N: R46.2, U8.18 (~Q), U37.AB9 (IO_L11N_T1_SRCC_33)
USCITA_FPGA_10_P: R45.1, U8.19 (Q), U37.AA9 (IO_L11P_T1_SRCC_33)
USCITA_FPGA_11_N: R54.2, U8.23 (~Q), U37.AC11 (IO_L13N_T2_MRCC_33)
USCITA_FPGA_11_P: R53.1, U8.22 (Q), U37.AB11 (IO_L13P_T2_MRCC_33)
USCITA_FPGA_12_N: R30.2, U9.2 (~Q), U37.AB10 (IO_L14N_T2_SRCC_33)
USCITA_FPGA_12_P: R29.1, U9.3 (Q), U37.AA10 (IO_L14P_T2_SRCC_33)
USCITA_FPGA_13_N: R33.2, U9.7 (~Q), U37.AC12 (IO_L15N_T2_DQS_33)
USCITA_FPGA_13_P: R32.1, U9.6 (Q), U37.AB12 (IO_L15P_T2_DQS_33)
USCITA_FPGA_14_N: R36.2, U9.18 (~Q), U37.AA12 (IO_L16N_T2_33)
USCITA_FPGA_14_P: R35.1, U9.19 (Q), U37.AA13 (IO_L16P_T2_33)
USCITA_FPGA_15_N: R57.2, U9.23 (~Q), U37.AD13 (IO_L17N_T2_33)
USCITA_FPGA_15_P: R56.1, U9.22 (Q), U37.AC13 (IO_L17P_T2_33)
VREF_2V5: C36.1, R60.1, R62.1, R64.1, R66.1, R68.1, R70.1, R72.1, R74.1, R76.1, R78.1, R80.1, R82.1, R84.1, R86.1, R88.1, R90.1, U22.6 (Vout), U24.8 (VREFIN/VREFOUT), U25.8 (VREFIN/VREFOUT)
